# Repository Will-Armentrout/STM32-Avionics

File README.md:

# STM32-Avionics
**Author: Will Armentrout**

The goal of this Repo was to complete sensor, STM32 Hardware Integration, telemetry display testing in preparation for creating a Custom Avionics PCB using the STM32 framework.

This Repo is broken into groups.
- Datasheets (where all the sensor and microcontroller datasheets are stored)
- Pinouts and Schematics (Where all Nucleo and sensor pinout/schematics are stored)
- Sensor Testing (Testbed folder for primative code to access sensor data and run servos)
- Telemetry and UI (Computer Side code for processing incoming sensor data from the microcontroller and displaying it to the user)

Let me know if there are any questions/recommendations! I am not a Computer Scientist/Engineer. I'm just a Mechanical Engineering Student looking to create more cool stuff.

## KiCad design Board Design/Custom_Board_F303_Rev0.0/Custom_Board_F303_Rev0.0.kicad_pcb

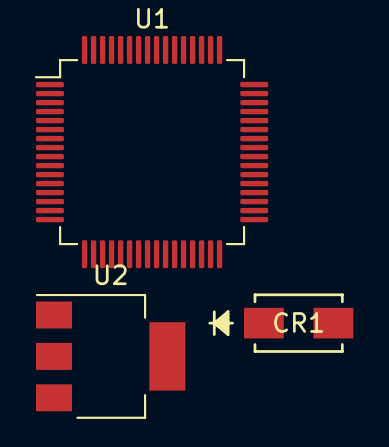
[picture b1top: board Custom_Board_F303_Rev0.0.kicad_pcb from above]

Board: 2 copper layers, 3 parts (0 on the bottom side), 3 nets, no tracks yet.

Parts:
CR1: STPS2L30A; SMA_STM
U1: STM32F303RETx; LQFP-64_10x10mm_P0.5mm
U2: LD1117S50TR_SOT223; SOT-223-3_TabPin2

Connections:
GND: U1.12 (VSSA), U1.18 (VSS), U1.31 (VSS), U1.47 (VSS), U1.63 (VSS), U2.1 (GND)
unnamed: CR1.1, U2.2 (VO)
VDD: U1.1 (VBAT), U1.19 (VDD), U1.32 (VDD), U1.48 (VDD), U1.64 (VDD)

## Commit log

2023-10-20 Added Datasheets for all test sensors
2023-11-02 Added sensor testing folder with files from CubeIDE for Temp and IMU/Gyro
2023-11-07 Finalized IMU Testing Code. Added code to access BMP280 Sensor
2023-11-08 Added Loop code to read raw pressure and temp data from BMP280.
2023-11-09 Added GPS Code Testing
2023-11-15 Added a Servo Motor Tester
2023-11-20 Fixed a polarity bug and added a levelshifter in the servo hardware circuit to bring PWM Signal to 6V
2023-11-28 Added movement testing for the micro servo.
2023-12-04 Recreated the Pressure Project after trying to use another driver. Should've forked
2023-12-05 Added Compensation Formula Variables
2023-12-05 Getting closer to solving the compensation issue.
2023-12-05 Fixed the Temperature and Pressure Compensation. BMP 280 Works!
2023-12-05 Added an altitude calculation.
2023-12-07 Added some Fixes to the GPS Code and Added a Python Script to read the Com port and Display the GPS Position.
2023-12-07 Changes to the README
2023-12-07 Changes to the README part 2
2023-12-07 Cleanup before branching.
2023-12-28 Added PCB Design Components in Kicad
2023-12-28 Added Schematic Components.
